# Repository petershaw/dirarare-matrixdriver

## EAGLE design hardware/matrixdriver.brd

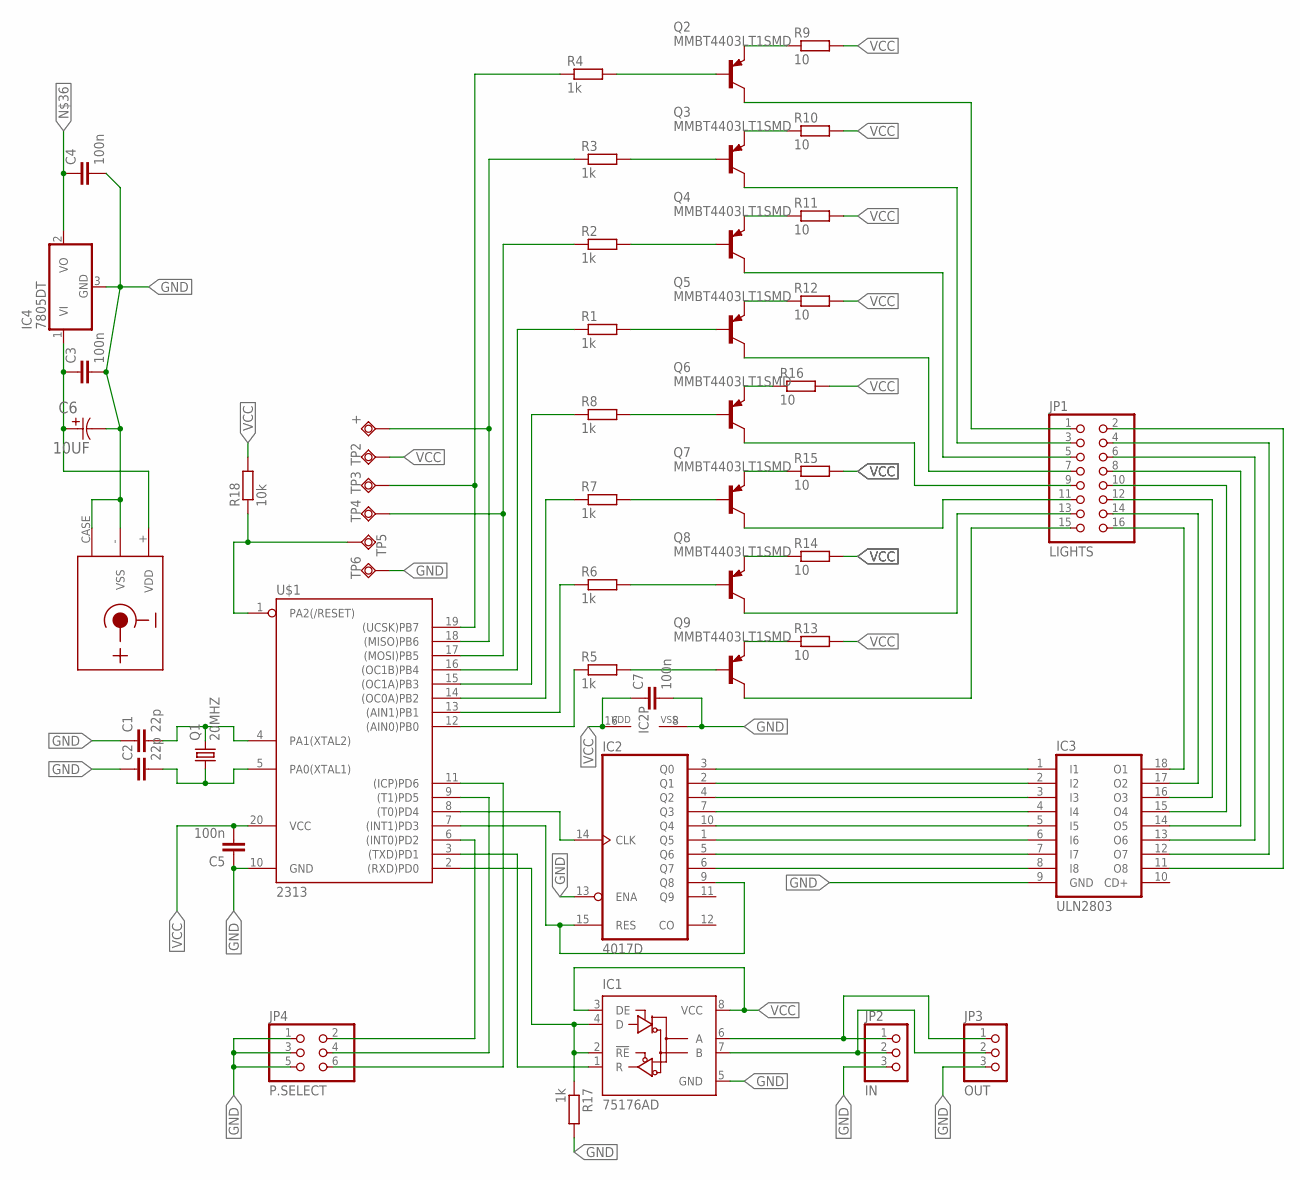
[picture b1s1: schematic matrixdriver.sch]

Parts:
+: TPSQTP20R; TP20R
C1, C2: 22p; C1206
C3, C4, C5, C7: 100n; C1206
C6: 10UF; CAPAE660X800N
IC1: 75176AD; D_R-PDSO-G8
IC2: 4017D; SO16
IC3: ULN2803; SO18W
IC4: 7805DT; TO252
JP1: LIGHTS; 2X08
JP2: IN; 1X03
JP3: OUT; 1X03
JP4: P.SELECT; 2X03
Q1: 20MHZ; HC49UP
Q2, Q3, Q4, Q5, Q6, Q7, Q8, Q9: MMBT4403LT1SMD; SOT23-BEC
R1, R2, R3, R4, R5, R6, R7, R8, R17: 1k; R1206
R9, R10, R11, R12, R13, R14, R15, R16: 10; R1206
R18: 10k; R1206
TP2: TPSQTP19SQ; TP19SQ
TP3, TP4, TP5, TP6: TPSQTP20SQ; TP20SQ
U$1: 2313; SO20L$
U$2: CUI_PJ-102A; CUI_DCJACK_PCB

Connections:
GND: C1.1, C2.1, C3.2, C4.2, C5.1, C6.2, C7.2, IC1.5 (GND), IC2.8 (VSS), IC2.13 (ENA), IC3.9 (GND), IC4.3 (GND), JP2.3, JP3.3, JP4.1, JP4.3, JP4.5, R17.2, TP6.TP, U$1.10 (GND), U$2.- (VSS), U$2.CASE
unnamed: R5.1, U$1.12 ((AIN0)PB0)
unnamed: R6.1, U$1.13 ((AIN1)PB1)
unnamed: R7.1, U$1.14 ((OC0A)PB2)
unnamed: R8.1, U$1.15 ((OC1A)PB3)
unnamed: R1.1, U$1.16 ((OC1B)PB4)
unnamed: R2.1, TP4.TP, U$1.17 ((MOSI)PB5)
unnamed: +.TP, R3.1, U$1.18 ((MISO)PB6)
unnamed: R4.1, TP3.TP, U$1.19 ((UCSK)PB7)
unnamed: IC1.1 (R), U$1.3 ((TXD)PD1)
unnamed: IC1.2 (!RE), IC1.4 (D), R17.1, U$1.2 ((RXD)PD0)
unnamed: C1.2, Q1.2, U$1.4 (PA1(XTAL2))
unnamed: C2.2, Q1.1, U$1.5 (PA0(XTAL1))
unnamed: JP1.9, Q6.C
unnamed: IC3.11 (O8), JP1.2
unnamed: IC2.14 (CLK), U$1.8 ((T0)PD4)
unnamed: IC2.9 (Q8), IC2.15 (RES), U$1.7 ((INT1)PD3)
unnamed: IC2.3 (Q0), IC3.1 (I1)
unnamed: IC2.2 (Q1), IC3.2 (I2)
unnamed: IC2.4 (Q2), IC3.3 (I3)
unnamed: IC2.7 (Q3), IC3.4 (I4)
unnamed: IC2.10 (Q4), IC3.5 (I5)
unnamed: IC2.1 (Q5), IC3.6 (I6)
unnamed: IC2.5 (Q6), IC3.7 (I7)
unnamed: IC2.6 (Q7), IC3.8 (I8)
unnamed: IC3.18 (O1), JP1.16
unnamed: IC3.17 (O2), JP1.14
unnamed: IC3.16 (O3), JP1.12
unnamed: IC3.15 (O4), JP1.10
unnamed: Q8.E, R14.1
unnamed: Q4.E, R11.1
unnamed: Q6.E, R16.1
unnamed: Q3.B, R3.2
unnamed: JP1.1, Q2.C
unnamed: Q9.E, R13.1
unnamed: Q7.E, R15.1
unnamed: C4.1, IC4.2 (VO)
unnamed: Q2.B, R4.2
unnamed: Q4.B, R2.2
unnamed: Q5.B, R1.2
unnamed: Q8.B, R6.2
unnamed: Q9.B, R5.2
unnamed: Q6.B, R8.2
unnamed: Q7.B, R7.2
unnamed: Q2.E, R9.1
unnamed: Q3.E, R10.1
unnamed: Q5.E, R12.1
unnamed: JP1.15, Q9.C
unnamed: JP1.13, Q8.C
unnamed: JP1.11, Q7.C
unnamed: JP1.7, Q5.C
unnamed: JP1.5, Q4.C
unnamed: JP1.3, Q3.C
unnamed: IC1.6 (A), JP2.1, JP3.1
unnamed: IC1.7 (B), JP2.2, JP3.2
unnamed: R18.1, TP5.TP, U$1.1 (PA2(/RESET))
unnamed: JP4.2, U$1.6 ((INT0)PD2)
unnamed: JP4.4, U$1.9 ((T1)PD5)
unnamed: JP4.6, U$1.11 ((ICP)PD6)
unnamed: IC3.12 (O7), JP1.4
unnamed: IC3.13 (O6), JP1.6
unnamed: C3.1, C6.1, IC4.1 (VI), U$2.+ (VDD)
unnamed: IC3.14 (O5), JP1.8
VCC: C5.2, C7.1, IC1.3 (DE), IC1.8 (VCC), IC2.16 (VDD), R9.2, R10.2, R11.2, R12.2, R13.2, R14.2, R15.2, R16.2, R18.2, TP2.TP, U$1.20 (VCC)

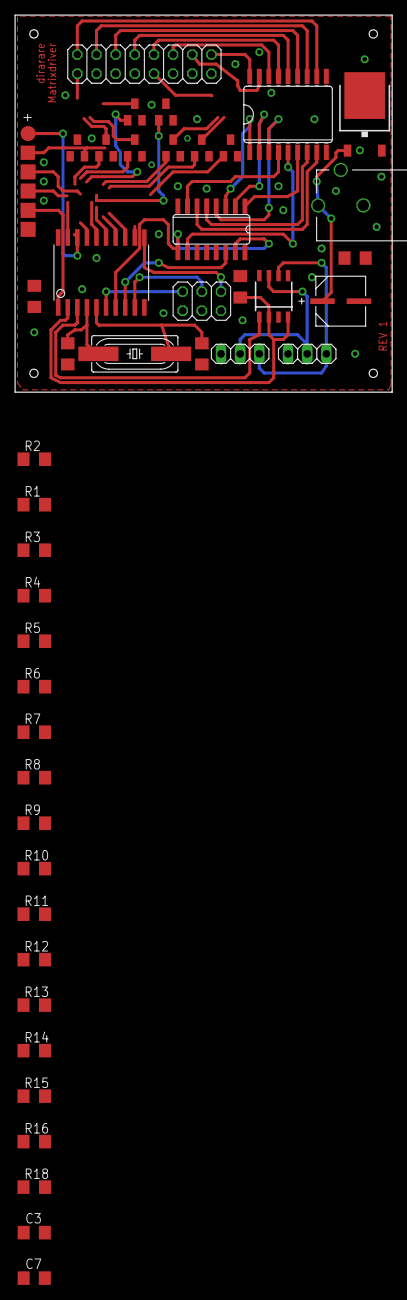
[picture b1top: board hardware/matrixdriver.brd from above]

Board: 2 copper layers, 50.0 x 50.0 mm, 50 parts (0 on the bottom side), 64 nets.

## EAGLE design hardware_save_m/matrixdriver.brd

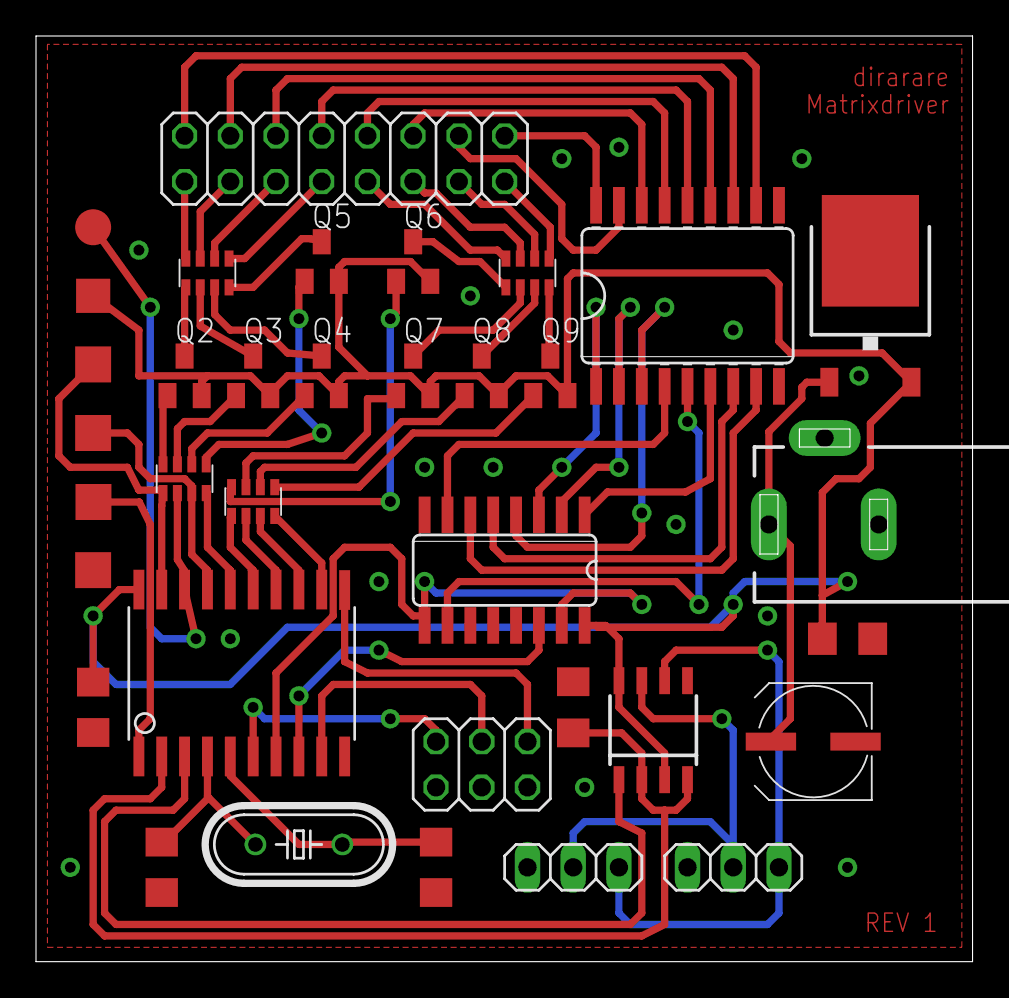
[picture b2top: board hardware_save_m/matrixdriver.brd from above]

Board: 2 copper layers, 52.0 x 51.4 mm, 35 parts (0 on the bottom side), 63 nets.

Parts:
C1, C2: 22p; C1206
C3: 100µ; UD-6,3X5,8_NICHICON
C4: 10µ; C1206
C5: 100n; C1206
CTS742C083_1, CTS742C083_2: 1k; CTS742C083
CTS742C083_3, CTS742C083_4: 10; CTS742C083
IC1: 75176AD; D_R-PDSO-G8
IC2: 4017D; SO16
IC3: ULN2803; SO18W
IC4: 7805DT; TO252
J1: DCJ0202
JP1: LIGHTS; 2X08
JP2: IN; 1X03
JP3: OUT; 1X03
JP4: P.SELECT; 2X03
Q2, Q3, Q4, Q5, Q6, Q7, Q8, Q9: MMBT4403LT1SMD; SOT23-BEC
Q10: 20MHZ; HC49/S
R17: 1k; R1206
TP1: TPSQTP20R; TP20R
TP2: TPSQTP19SQ; TP19SQ
TP3, TP4, TP5, TP6: TPSQTP20SQ; TP20SQ
U$1: TINY2313; SO20L$

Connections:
GND: C1.1, C2.1, C3.-, C4.2, C5.1, IC1.5, IC2.8, IC2.13, IC3.9, IC4.3, J1.3, JP2.3, JP3.3, JP4.1, JP4.3, JP4.5, R17.2, TP6.TP, U$1.10
unnamed: CTS742C083_2.4, U$1.12
unnamed: CTS742C083_2.3, U$1.13
unnamed: CTS742C083_2.2, U$1.14
unnamed: CTS742C083_2.1, U$1.15
unnamed: CTS742C083_1.4, U$1.16
unnamed: CTS742C083_1.3, TP4.TP, U$1.17
unnamed: CTS742C083_1.2, TP1.TP, U$1.18
unnamed: CTS742C083_1.1, TP3.TP, U$1.19
unnamed: IC1.1, U$1.3
unnamed: IC1.2, IC1.4, R17.1, U$1.2
unnamed: C1.2, Q10.2, U$1.4
unnamed: C2.2, Q10.1, U$1.5
unnamed: CTS742C083_4.8, JP1.9
unnamed: IC3.11, JP1.2
unnamed: IC2.14, U$1.8
unnamed: IC2.9, IC2.15, U$1.7
unnamed: IC2.3, IC3.1
unnamed: IC2.2, IC3.2
unnamed: IC2.4, IC3.3
unnamed: IC2.7, IC3.4
unnamed: IC2.10, IC3.5
unnamed: IC2.1, IC3.6
unnamed: IC2.5, IC3.7
unnamed: IC2.6, IC3.8
unnamed: IC3.18, JP1.16
unnamed: IC3.17, JP1.14
unnamed: IC3.16, JP1.12
unnamed: IC3.15, JP1.10
unnamed: CTS742C083_4.7, JP1.11
unnamed: CTS742C083_4.6, JP1.13
unnamed: CTS742C083_4.5, JP1.15
unnamed: CTS742C083_1.7, Q3.B
unnamed: CTS742C083_3.8, JP1.1
unnamed: CTS742C083_3.7, JP1.3
unnamed: CTS742C083_3.6, JP1.5
unnamed: CTS742C083_3.5, JP1.7
unnamed: CTS742C083_1.8, Q2.B
unnamed: CTS742C083_1.6, Q4.B
unnamed: CTS742C083_1.5, Q5.B
unnamed: CTS742C083_2.6, Q8.B
unnamed: CTS742C083_2.5, Q9.B
unnamed: CTS742C083_2.8, Q6.B
unnamed: CTS742C083_2.7, Q7.B
unnamed: CTS742C083_4.4, Q9.C
unnamed: CTS742C083_4.3, Q8.C
unnamed: CTS742C083_4.2, Q7.C
unnamed: CTS742C083_4.1, Q6.C
unnamed: CTS742C083_3.4, Q5.C
unnamed: CTS742C083_3.3, Q4.C
unnamed: CTS742C083_3.2, Q3.C
unnamed: CTS742C083_3.1, Q2.C
unnamed: IC1.6, JP2.1, JP3.1
unnamed: IC1.7, JP2.2, JP3.2
unnamed: TP5.TP, U$1.1
unnamed: JP4.2, U$1.6
unnamed: JP4.4, U$1.9
unnamed: JP4.6, U$1.11
unnamed: IC3.12, JP1.4
unnamed: IC3.13, JP1.6
unnamed: C3.+, IC4.1, J1.1
unnamed: IC3.14, JP1.8
VCC: C4.1, C5.2, IC1.3, IC1.8, IC2.16, IC4.2, Q2.E, Q3.E, Q4.E, Q5.E, Q6.E, Q7.E, Q8.E, Q9.E, TP2.TP, U$1.20

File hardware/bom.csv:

"Part";"Value";"Device";"Package";"Description";"MF";"MPN";"OC_FARNELL";"OC_NEWARK";"TP_SIGNAL_NAME";
"C1";"22p";"C-EUC1206";"C1206";"CAPACITOR, European symbol";"";"";"";"";"";
"C2";"22p";"C-EUC1206";"C1206";"CAPACITOR, European symbol";"";"";"";"";"";
"C3";"100µ";"CPOL-USUD-6,3X5,8";"UD-6,3X5,8_NICHICON";"POLARIZED CAPACITOR, American symbol";"";"";"";"";"";
"C4";"10µ";"C-EUC1206";"C1206";"CAPACITOR, European symbol";"";"";"";"";"";
"CTS742C083_1";"1k";"CTS742C083";"CTS742C083";"Chip Resistor Array 4 Single Resistor";"";"";"";"";"";
"CTS742C083_2";"1k";"CTS742C083";"CTS742C083";"Chip Resistor Array 4 Single Resistor";"";"";"";"";"";
"CTS742C083_3";"10";"CTS742C083";"CTS742C083";"Chip Resistor Array 4 Single Resistor";"";"";"";"";"";
"CTS742C083_4";"10";"CTS742C083";"CTS742C083";"Chip Resistor Array 4 Single Resistor";"";"";"";"";"";
"IC1";"75176AD";"75176AD";"D_R-PDSO-G8";"DIFFERENTIAL BUS TRANSCEIVER";"";"";"";"";"";
"IC2";"4017D";"4017D";"SO16";"COUNTER/DIVIDER";"";"";"";"";"";
"IC3";"ULN2803";"ULN2803ASMD";"SO18W";"DRIVER ARRAY";"";"";"";"";"";
"IC4";"7805DT";"7805DT";"TO252";"Positive VOLTAGE REGULATOR";"";"";"";"";"";
"J1";"DCJ0202";"DCJ0202";"DCJ0202";"DC POWER JACK";"";"";"unknown";"unknown";"";
"JP1";"LIGHTS";"PINHD-2X8_2.54";"2X08";"PIN HEADER";"";"";"";"";"";
"JP2";"IN";"PINHD-1X3";"1X03";"PIN HEADER";"";"";"";"";"";
"JP3";"OUT";"PINHD-1X3";"1X03";"PIN HEADER";"";"";"";"";"";
"JP4";"P.SELECT";"PINHD-2X3";"2X03";"PIN HEADER";"";"";"";"";"";
"Q2";"MMBT4403LT1SMD";"MMBT4403LT1SMD";"SOT23-BEC";"PNP Transistror";"";"";"";"";"";
"Q3";"MMBT4403LT1SMD";"MMBT4403LT1SMD";"SOT23-BEC";"PNP Transistror";"";"";"";"";"";
"Q4";"MMBT4403LT1SMD";"MMBT4403LT1SMD";"SOT23-BEC";"PNP Transistror";"";"";"";"";"";
"Q5";"MMBT4403LT1SMD";"MMBT4403LT1SMD";"SOT23-BEC";"PNP Transistror";"";"";"";"";"";
"Q6";"MMBT4403LT1SMD";"MMBT4403LT1SMD";"SOT23-BEC";"PNP Transistror";"";"";"";"";"";
"Q7";"MMBT4403LT1SMD";"MMBT4403LT1SMD";"SOT23-BEC";"PNP Transistror";"";"";"";"";"";
"Q8";"MMBT4403LT1SMD";"MMBT4403LT1SMD";"SOT23-BEC";"PNP Transistror";"";"";"";"";"";
"Q9";"MMBT4403LT1SMD";"MMBT4403LT1SMD";"SOT23-BEC";"PNP Transistror";"";"";"";"";"";
"Q10";"20MHZ";"CRYSTALHC49S";"HC49/S";"CRYSTAL";"";"";"1667008";"unknown";"";
"R17";"1k";"R-EU_R1206";"R1206";"RESISTOR, European symbol";"";"";"";"";"";
"TP1";"TPSQTP20R";"TPSQTP20R";"TP20R";"Test pad";"";"";"";"";"";
"TP2";"TPSQTP19SQ";"TPSQTP19SQ";"TP19SQ";"Test pad";"";"";"";"";"";
"TP3";"TPSQTP20SQ";"TPSQTP20SQ";"TP20SQ";"Test pad";"";"";"";"";"";
"TP4";"TPSQTP20SQ";"TPSQTP20SQ";"TP20SQ";"Test pad";"";"";"";"";"";
"TP5";"TPSQTP20SQ";"TPSQTP20SQ";"TP20SQ";"Test pad";"";"";"";"";"";
"TP6";"TPSQTP20SQ";"TPSQTP20SQ";"TP20SQ";"Test pad";"";"";"";"";"";
"U$1";"TINY2313";"TINY2313-*S*";"SO20L$";"Atmel Tiny2313";"";"";"";"";"";

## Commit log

2014-08-02 initial add
    fix dmx adress
2014-08-02 set project name
2014-08-07 add schematic
2014-08-08 more schematic
2014-08-08 Connect the basic elements
2014-08-08 first final schematic
2014-08-08 Fix Schematic ERC rrors
2014-08-09 Add first board layout
2014-08-10 Fully routed board
2014-08-10 add mounting holes
2014-08-15 working on a finalised board
2014-08-16 working on finishing
2014-08-21 working on board finalisation
2014-08-21 save board variation, fix float
2014-08-21 working on partlist
    add numbers document with parts from digikey
2014-08-25 fix some layout errors
2014-08-25 finish digikey ordersheet
2014-09-09 working on 50/50 board
    - shrinking
2014-09-09 resize to 5050
2014-09-11 move some elements
2014-09-12 Release Candidate
2014-09-14 REV.1 Finalisation
2014-09-18 add production images
2014-09-29 add gerber data
2014-11-20 swap output port
2014-11-20 add production files
2014-11-20 Hexfile
2015-01-01 debug session
2015-01-29 Fix errors behind transistor
2015-01-29 fix some errors in schema
2015-03-06 working on Hardware Revision 2 - fix pullup
2015-03-19 Revert "debug session"
    This reverts commit 6a6f3644e13fca41bd383cc3dccbf02b4444f1f5.
2015-04-16 Set fusebits with make fuse
2015-04-21 work on schematics
2015-04-21 transistor block changed
2015-04-22 Beschriftungen angepasst
2015-04-29 Add readfuse target
2015-07-28 board changes without resistor at base
